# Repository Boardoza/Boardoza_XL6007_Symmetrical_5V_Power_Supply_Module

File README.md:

# Boardoza XL6007 Symmetrical ±5V Power Supply Module

The **Boardoza XL6007** is a high-efficiency **DC-DC step-up switching regulator module** designed to generate a **symmetrical ±5V output** from a **single supply** input source. Built around the **XL6007E1** high-frequency switching regulator, this board provides both +5V and -5V outputs, making it ideal for analog and dual-supply applications.

Thanks to its fixed **400kHz switching frequency** and integrated boost converter topology, the module ensures stable, efficient voltage conversion with minimal external components. The symmetrical output capability allows balanced current draw from both rails, supporting up to **500mA total output current**. This makes it especially suitable for operational amplifier circuits, sensor interfaces, audio preamplifiers, and other low-power analog designs requiring dual-polarity supply.

## [Click here to purchase!](https://www.ozdisan.com/ureticiler/boardoza)

| Front Side | Back Side |
|:---:|:---:|
|  |  |

---

## Key Features

- **Symmetrical ±5V Output:** Generates both **+5V and -5V** from a single input supply.  
- **Boost Converter Topology:** Based on the **XL6007E1** high-efficiency DC-DC step-up regulator.  
- **High Output Capability:** Supports up to **500mA total output current** (shared between outputs).  
- **High Switching Frequency:** Fixed **400kHz** operation for stable and efficient performance.  
- **Good Efficiency:** Up to **~90% efficiency** depending on load and conditions.  

---

## Technical Specifications

**Model:** XL6007  
**Manufacturer:** Boardoza  
**Manufacturer IC:** XLSEMI  
**Topology:** Boost Switching Regulator (Configured for Dual Output)  
**Input Voltage:** 3V DC to +12V DC  
**Output Voltage:** +5V and -5V  
**Maximum Output Current:** Up to 500mA (Total Symmetrical)  
**Switching Frequency:** 400kHz (Fixed)  
**Efficiency:** Up to 90% (IC dependent, application specific)  
**Operating Temperature:** -40°C to +125°C  
**Board Dimensions:** 40mm x 60mm  

---

## Board Pinout

### ( J1 ) Input Connector

| Pin Number | Pin Name | Description |
|:---:|:---:|---|
| 1 | VIN | Supply Voltage Input |
| 2 | GND | Ground |

### ( J2 ) Output Connector

| Pin Number | Pin Name | Description |
|:---:|:---:|---|
| 1 | +5V | Positive 5V Output |
| 2 | GND | Ground |
| 3 | -5V | Negative 5V Output |

---

## Performance Graph

### Output Current vs Input Voltage

---

## Board Dimensions

---

## Step Files

[Boardoza XL6007E1.step](./assets/XL6007%20Step.step)

---

## Datasheet

[XL6007 Datasheet.pdf](./assets/XL6007%20Datasheet.pdf)

---

## Version History

- V1.0.0 - Initial Release

---

## Support

- If you have any questions or need support, please contact **support@boardoza.com**

---

## **License**
### **Hardware Design**

[![CC BY-SA 4.0][cc-by-sa-shield]][cc-by-sa]

All hardware design files are licensed under [Creative Commons Attribution-ShareAlike 4.0 International License][cc-by-sa].

[cc-by-sa]: http://creativecommons.org/licenses/by-sa/4.0/
[cc-by-sa-shield]: https://img.shields.io/badge/License-CC%20BY--SA%204.0-lightgrey.svg

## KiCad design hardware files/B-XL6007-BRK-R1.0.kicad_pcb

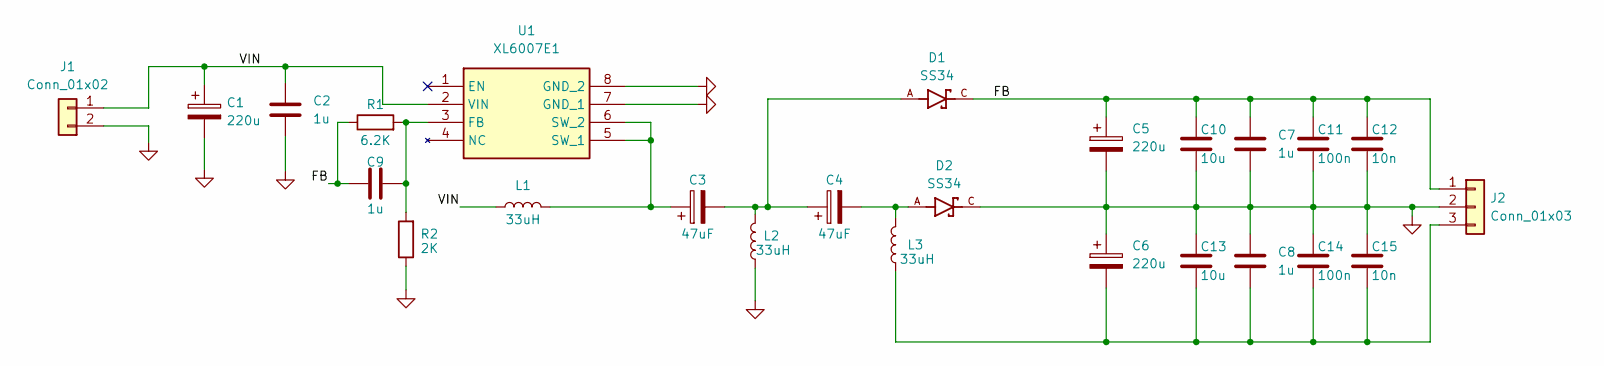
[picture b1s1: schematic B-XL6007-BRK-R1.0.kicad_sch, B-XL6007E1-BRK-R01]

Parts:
C1, C5, C6: 220u; CP_Elec_8.3x8.3; MPN SVB025M221FABPE50V00A
C2, C7, C8, C9: 1u; C_0603_1608Metric; MPN MCF03KTB250105
C3, C4: 47uF; CP_Elec_6.3x7.7; MPN SC1H476M6L07KVR
C10, C13: 10u; C_0603_1608Metric; MPN MCF03MTX250106
C11, C14: 100n; C_0603_1608Metric; MPN MCF03KTB250104
C12, C15: 10n; C_0603_1608Metric; MPN MCF03KTB500103
D1, D2: SS34; DIO_SS34; PARTREV S2311
J1: Conn_01x02; 2317-02S_1x02_P2.50mm_Vertical; MPN 2317-02S
J2: Conn_01x03; 2317-03S_1x03_P2.50mm_Vertical; MPN 2317-03S
L1, L2, L3: 33uH; L_10.4x10.4_H4.8; MPN CDRH105R-330M
R1: 6.2K; R_0603_1608Metric; MPN 0603SAJ0622T5E
R2: 2K; R_0603_1608Metric; MPN 0603SAJ0202T5E
U1: XL6007E1; SOIC127P600X175-8N; Manufacturer_Part_Number XL6007E1

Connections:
/FB: C5.1, C7.1, C9.1, C10.1, C11.1, C12.1, D1.C, J2.1, R1.1
/VIN: C1.1, C2.1, J1.1, L1.1, U1.2 (VIN)
GND: C1.2, C2.2, C5.2, C6.1, C7.2, C8.1, C10.2, C11.2, C12.2, C13.1, C14.1, C15.1, D2.C, J1.2, J2.2, L2.1, R2.1, U1.7 (GND_1), U1.8 (GND_2)
unnamed: C3.2, C4.1, D1.A, L2.2
unnamed: C4.2, D2.A, L3.2
unnamed: C6.2, C8.2, C13.2, C14.2, C15.2, J2.3, L3.1
unnamed: C9.2, R1.2, R2.2, U1.3 (FB)
unnamed: C3.1, L1.2, U1.5 (SW_1), U1.6 (SW_2)

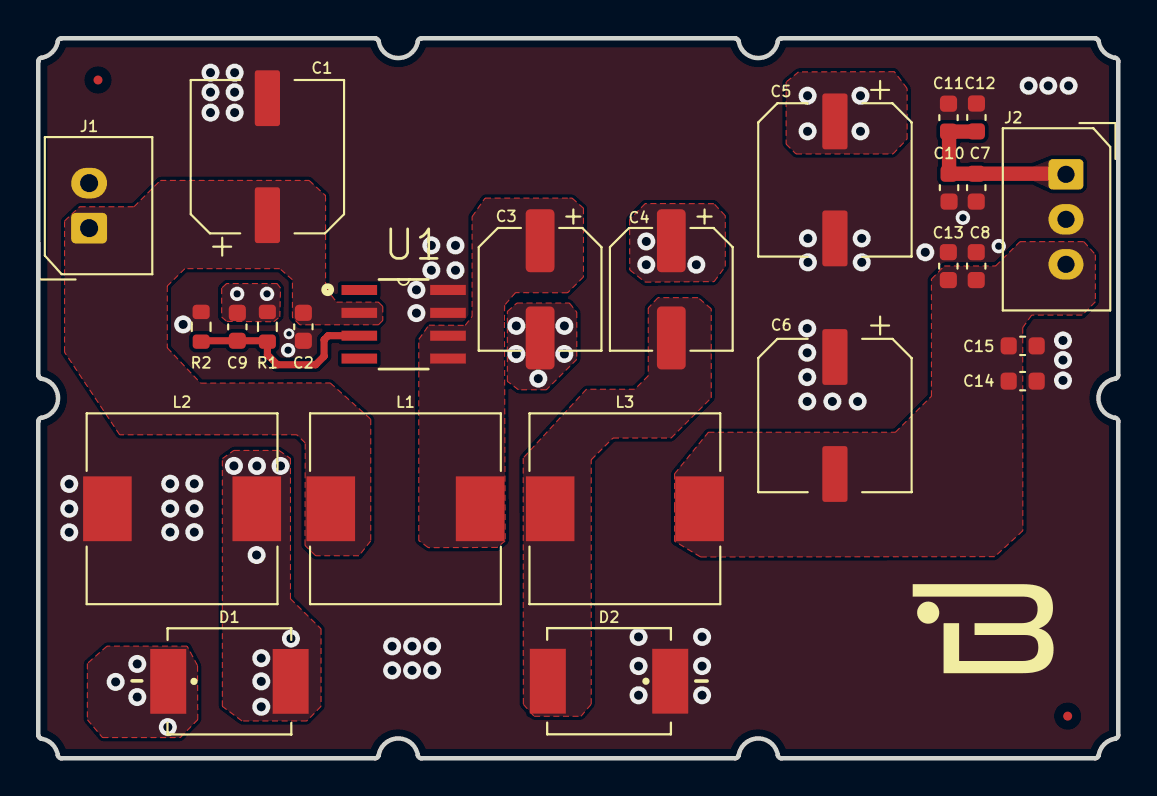
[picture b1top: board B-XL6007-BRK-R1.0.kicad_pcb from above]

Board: 2 copper layers, 60.0 x 40.0 mm, 25 parts (0 on the bottom side), 8 nets.
